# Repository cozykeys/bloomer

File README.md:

# CozyKeys Bloomer

This repository contains the design files for the CozyKeys Bloomer, an 87-key
ergonomic mechanical keyboard.

This keyboard has undergone several revisions and name changes. Previous names
were *Atreus87* and *Ergo87* and artifacts of these may still be present in the
repository.

## Firmware

- [Bloomer rev2](https://github.com/cozykeys/qmk_firmware/tree/bloomer_v2)
- [Bloomer rev3](https://github.com/cozykeys/qmk_firmware/tree/bloomer_v3)

## Project Status

### rev0

The first revision of the board was hand-wired and built as a proof of concept
to ensure that the layout is comfortable.

### rev1

The second revision added a PCB and a complete redesign of the case so that the
PCB would fit accurately.

This initial PCB was functional but lacked any RGB support. It also had a few
issues:
- When placing the ItsyBitsy upside down to reduce the height needed between
  the switch plate and bottom plate, there is no easy way to access RST
- Switch footprints were "flippable" which was misleading as the controller
  pinout only supported a single orientation

### rev2

The second revision added several features and fixes:
- Dedicated reset button with the case updated to make this accessible
- Single orientation switch footprints
- RGB underglow support

[Rev2 Build Guide](./revisions/rev2/README.md)

### rev3 (REDACTED)

See: [v3.0 README](./v3.0/README.md)

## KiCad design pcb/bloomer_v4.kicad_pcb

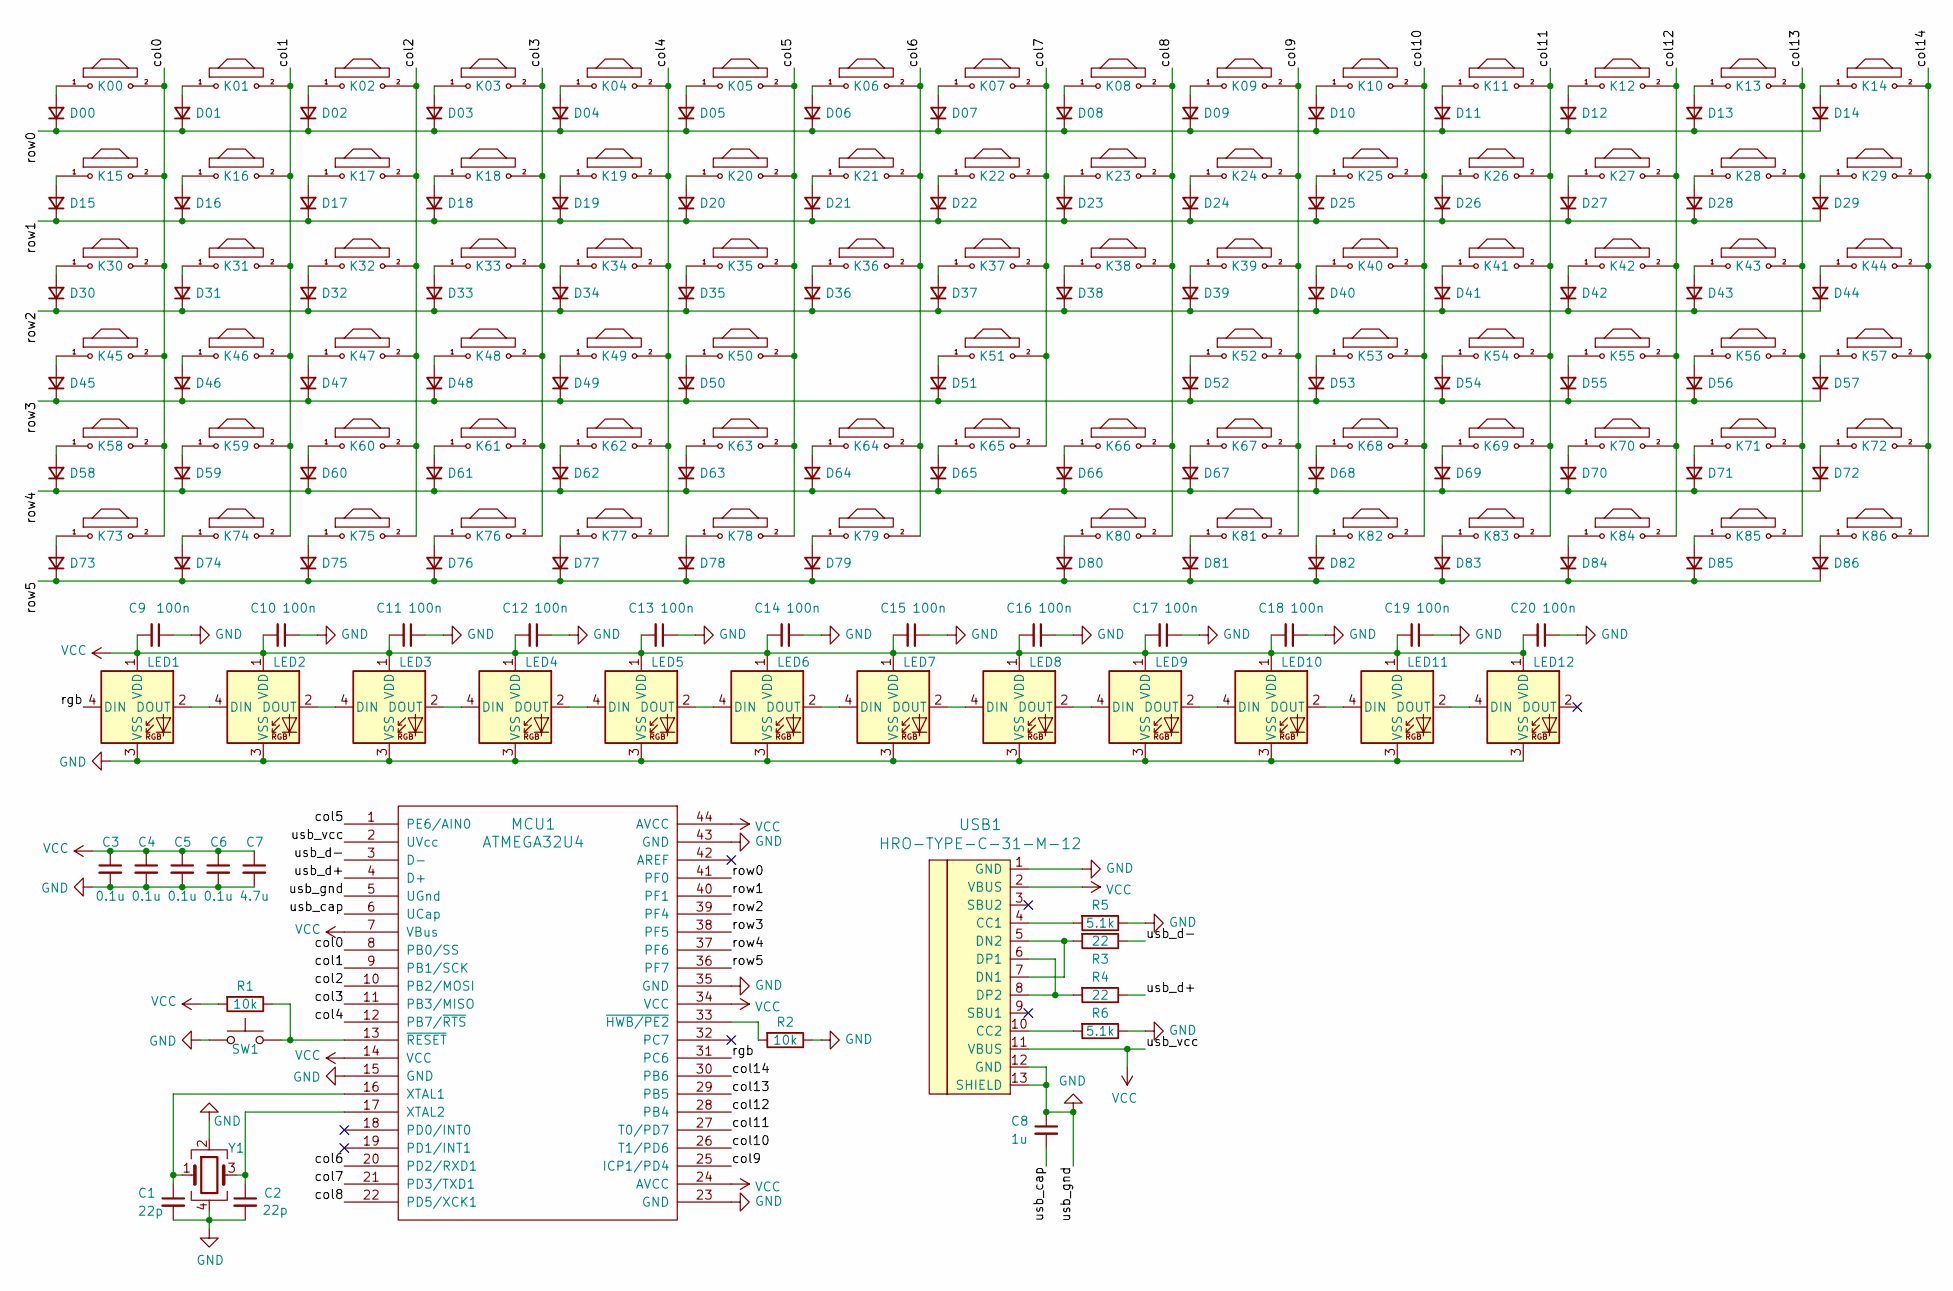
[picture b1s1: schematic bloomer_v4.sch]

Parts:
C1, C2: 22p; C_0805_2012Metric_Pad1.18x1.45mm_HandSolder
C3, C4, C5, C6: 0.1u; C_0805_2012Metric_Pad1.18x1.45mm_HandSolder
C7: 4.7u; C_0805_2012Metric_Pad1.18x1.45mm_HandSolder
C8: 1u; C_0805_2012Metric_Pad1.18x1.45mm_HandSolder
C9, C10, C11, C12, C13, C14, C15, C16, C17, C18, C19, C20: 100n; C_0805_2012Metric_Pad1.18x1.45mm_HandSolder
D00, D01, D02, D03, D04, D05, D06, D07, D08, D09, D10, D11, D12, D13, D14, D15, D16, D17, D18, D19, D20, D21, D22, D23, D24, D25, D26, D27, D28, D29, D30, D31, D32, D33, D34, D35, D36, D37, D38, D39, D40, D41, D42, D43, D44, D45, D46, D47, D48, D49, D50, D51, D52, D53, D54, D55, D56, D57, D58, D59, D60, D61, D62, D63, D64, D65, D66, D67, D68, D69, D70, D71, D72, D73, D74, D75, D76, D77, D78, D79, D80, D81, D82, D83, D84, D85, D86: D_Small; Diode-dual
K00, K01, K02, K03, K04, K05, K06, K07, K08, K09, K10, K11, K12, K13, K14, K15, K16, K17, K18, K19, K20, K21, K22, K23, K24, K25, K26, K27, K28, K29, K30, K31, K32, K33, K34, K35, K36, K37, K38, K39, K40, K41, K42, K43, K44, K45, K46, K47, K48, K49, K50, K51, K52, K53, K54, K55, K56, K57, K58, K59, K60, K61, K62, K63, K64, K65, K66, K67, K68, K69, K70, K71, K72, K73, K74, K75, K76, K77, K78, K79, K80, K81, K82, K83, K84, K85, K86: MX; MX_1.00u
LED1, LED2, LED3, LED4, LED5, LED6, LED7, LED8, LED9, LED10, LED11, LED12: WS2812B; LED_WS2812B_PLCC4_5.0x5.0mm_P3.2mm
MCU1: ATMEGA32U4; ATMEGA32U4-AU
R1, R2: 10k; R_0805_2012Metric_Pad1.20x1.40mm_HandSolder
R3, R4: 22; R_0805_2012Metric_Pad1.20x1.40mm_HandSolder
R5, R6: 5.1k; R_0805_2012Metric_Pad1.20x1.40mm_HandSolder
SW1: SW_Push; SW_TH_Tactile_Omron_B3F-10xx_Centered
USB1: HRO-TYPE-C-31-M-12; HRO-TYPE-C-31-M-12-Assembly
Y1: Crystal_GND24; Crystal_SMD_SeikoEpson_FA238-4Pin_3.2x2.5mm_HandSoldering

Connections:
/col0: K00.2, K15.2, K30.2, K45.2, K58.2, K73.2, MCU1.8 (PB0/SS)
/col1: K01.2, K16.2, K31.2, K46.2, K59.2, K74.2, MCU1.9 (PB1/SCK)
/col2: K02.2, K17.2, K32.2, K47.2, K60.2, K75.2, MCU1.10 (PB2/MOSI)
/col3: K03.2, K18.2, K33.2, K48.2, K61.2, K76.2, MCU1.11 (PB3/MISO)
/col4: K04.2, K19.2, K34.2, K49.2, K62.2, K77.2, MCU1.12 (PB7/~RTS)
/col5: K05.2, K20.2, K35.2, K50.2, K63.2, K78.2, MCU1.1 (PE6/AIN0)
/col6: K06.2, K21.2, K36.2, K64.2, K79.2, MCU1.20 (PD2/RXD1)
/col7: K07.2, K22.2, K37.2, K51.2, K65.2, MCU1.21 (PD3/TXD1)
/col8: K08.2, K23.2, K38.2, K66.2, K80.2, MCU1.22 (PD5/XCK1)
/col9: K09.2, K24.2, K39.2, K52.2, K67.2, K81.2, MCU1.25 (ICP1/PD4)
/col10: K10.2, K25.2, K40.2, K53.2, K68.2, K82.2, MCU1.26 (T1/PD6)
/col11: K11.2, K26.2, K41.2, K54.2, K69.2, K83.2, MCU1.27 (T0/PD7)
/col12: K12.2, K27.2, K42.2, K55.2, K70.2, K84.2, MCU1.28 (PB4)
/col13: K13.2, K28.2, K43.2, K56.2, K71.2, K85.2, MCU1.29 (PB5)
/col14: K14.2, K29.2, K44.2, K57.2, K72.2, K86.2, MCU1.30 (PB6)
/rgb: LED1.4 (DIN), MCU1.31 (PC6)
/row0: D00.1 (K), D01.1 (K), D02.1 (K), D03.1 (K), D04.1 (K), D05.1 (K), D06.1 (K), D07.1 (K), D08.1 (K), D09.1 (K), D10.1 (K), D11.1 (K), D12.1 (K), D13.1 (K), D14.1 (K), MCU1.41 (PF0)
/row1: D15.1 (K), D16.1 (K), D17.1 (K), D18.1 (K), D19.1 (K), D20.1 (K), D21.1 (K), D22.1 (K), D23.1 (K), D24.1 (K), D25.1 (K), D26.1 (K), D27.1 (K), D28.1 (K), D29.1 (K), MCU1.40 (PF1)
/row2: D30.1 (K), D31.1 (K), D32.1 (K), D33.1 (K), D34.1 (K), D35.1 (K), D36.1 (K), D37.1 (K), D38.1 (K), D39.1 (K), D40.1 (K), D41.1 (K), D42.1 (K), D43.1 (K), D44.1 (K), MCU1.39 (PF4)
/row3: D45.1 (K), D46.1 (K), D47.1 (K), D48.1 (K), D49.1 (K), D50.1 (K), D51.1 (K), D52.1 (K), D53.1 (K), D54.1 (K), D55.1 (K), D56.1 (K), D57.1 (K), MCU1.38 (PF5)
/row4: D58.1 (K), D59.1 (K), D60.1 (K), D61.1 (K), D62.1 (K), D63.1 (K), D64.1 (K), D65.1 (K), D66.1 (K), D67.1 (K), D68.1 (K), D69.1 (K), D70.1 (K), D71.1 (K), D72.1 (K), MCU1.37 (PF6)
/row5: D73.1 (K), D74.1 (K), D75.1 (K), D76.1 (K), D77.1 (K), D78.1 (K), D79.1 (K), D80.1 (K), D81.1 (K), D82.1 (K), D83.1 (K), D84.1 (K), D85.1 (K), D86.1 (K), MCU1.36 (PF7)
/usb_cap: C8.2, MCU1.6 (UCap)
/usb_d+: MCU1.4 (D+), R4.1
/usb_d-: MCU1.3 (D-), R3.1
GND: C1.2, C2.2, C3.2, C4.2, C5.2, C6.2, C7.2, C8.1, C9.1, C10.1, C11.1, C12.1, C13.1, C14.1, C15.1, C16.1, C17.1, C18.1, C19.1, C20.1, LED1.3 (VSS), LED2.3 (VSS), LED3.3 (VSS), LED4.3 (VSS), LED5.3 (VSS), LED6.3 (VSS), LED7.3 (VSS), LED8.3 (VSS), LED9.3 (VSS), LED10.3 (VSS), LED11.3 (VSS), LED12.3 (VSS), MCU1.5 (UGnd), MCU1.15 (GND), MCU1.23 (GND), MCU1.35 (GND), MCU1.43 (GND), R2.1, R5.1, R6.1, SW1.1, USB1.1 (GND), USB1.12 (GND), USB1.13 (SHIELD), Y1.2, Y1.4
unnamed: C1.1, MCU1.16 (XTAL1), Y1.1
unnamed: C2.1, MCU1.17 (XTAL2), Y1.3
unnamed: D00.2 (A), K00.1
unnamed: D01.2 (A), K01.1
unnamed: D02.2 (A), K02.1
unnamed: D03.2 (A), K03.1
unnamed: D04.2 (A), K04.1
unnamed: D05.2 (A), K05.1
unnamed: D06.2 (A), K06.1
unnamed: D07.2 (A), K07.1
unnamed: D08.2 (A), K08.1
unnamed: D09.2 (A), K09.1
unnamed: D10.2 (A), K10.1
unnamed: D11.2 (A), K11.1
unnamed: D12.2 (A), K12.1
unnamed: D13.2 (A), K13.1
unnamed: D14.2 (A), K14.1
unnamed: D15.2 (A), K15.1
unnamed: D16.2 (A), K16.1
unnamed: D17.2 (A), K17.1
unnamed: D18.2 (A), K18.1
unnamed: D19.2 (A), K19.1
unnamed: D20.2 (A), K20.1
unnamed: D21.2 (A), K21.1
unnamed: D22.2 (A), K22.1
unnamed: D23.2 (A), K23.1
unnamed: D24.2 (A), K24.1
unnamed: D25.2 (A), K25.1
unnamed: D26.2 (A), K26.1
unnamed: D27.2 (A), K27.1
unnamed: D28.2 (A), K28.1
unnamed: D29.2 (A), K29.1
unnamed: D30.2 (A), K30.1
unnamed: D31.2 (A), K31.1
unnamed: D32.2 (A), K32.1
unnamed: D33.2 (A), K33.1
unnamed: D34.2 (A), K34.1
unnamed: D35.2 (A), K35.1
unnamed: D36.2 (A), K36.1
unnamed: D37.2 (A), K37.1
unnamed: D38.2 (A), K38.1
unnamed: D39.2 (A), K39.1
unnamed: D40.2 (A), K40.1
unnamed: D41.2 (A), K41.1
unnamed: D42.2 (A), K42.1
unnamed: D43.2 (A), K43.1
unnamed: D44.2 (A), K44.1
unnamed: D45.2 (A), K45.1
unnamed: D46.2 (A), K46.1
unnamed: D47.2 (A), K47.1
unnamed: D48.2 (A), K48.1
unnamed: D49.2 (A), K49.1
unnamed: D50.2 (A), K50.1
unnamed: D51.2 (A), K51.1
unnamed: D52.2 (A), K52.1
unnamed: D53.2 (A), K53.1
unnamed: D54.2 (A), K54.1
unnamed: D55.2 (A), K55.1
unnamed: D56.2 (A), K56.1
unnamed: D57.2 (A), K57.1
unnamed: D58.2 (A), K58.1
unnamed: D59.2 (A), K59.1
unnamed: D60.2 (A), K60.1
unnamed: D61.2 (A), K61.1
unnamed: D62.2 (A), K62.1
unnamed: D63.2 (A), K63.1
unnamed: D64.2 (A), K64.1
unnamed: D65.2 (A), K65.1
unnamed: D66.2 (A), K66.1
unnamed: D67.2 (A), K67.1
unnamed: D68.2 (A), K68.1
unnamed: D69.2 (A), K69.1
unnamed: D70.2 (A), K70.1
unnamed: D71.2 (A), K71.1
unnamed: D72.2 (A), K72.1
unnamed: D73.2 (A), K73.1
unnamed: D74.2 (A), K74.1
unnamed: D75.2 (A), K75.1
unnamed: D76.2 (A), K76.1
unnamed: D77.2 (A), K77.1
unnamed: D78.2 (A), K78.1
unnamed: D79.2 (A), K79.1
unnamed: D80.2 (A), K80.1
unnamed: D81.2 (A), K81.1
unnamed: D82.2 (A), K82.1
unnamed: D83.2 (A), K83.1
unnamed: D84.2 (A), K84.1
unnamed: D85.2 (A), K85.1
unnamed: D86.2 (A), K86.1
unnamed: LED1.2 (DOUT), LED2.4 (DIN)
unnamed: LED2.2 (DOUT), LED3.4 (DIN)
unnamed: LED3.2 (DOUT), LED4.4 (DIN)
unnamed: LED4.2 (DOUT), LED5.4 (DIN)
unnamed: LED5.2 (DOUT), LED6.4 (DIN)
unnamed: LED6.2 (DOUT), LED7.4 (DIN)
unnamed: LED7.2 (DOUT), LED8.4 (DIN)
unnamed: LED8.2 (DOUT), LED9.4 (DIN)
unnamed: LED10.2 (DOUT), LED11.4 (DIN)
unnamed: LED9.2 (DOUT), LED10.4 (DIN)
unnamed: LED11.2 (DOUT), LED12.4 (DIN)
unnamed: MCU1.13 (~RESET), R1.1, SW1.2
unnamed: MCU1.33 (~HWB/PE2), R2.2
unnamed: R3.2, USB1.5 (DN2), USB1.7 (DN1)
unnamed: R4.2, USB1.6 (DP1), USB1.8 (DP2)
unnamed: R5.2, USB1.4 (CC1)
unnamed: R6.2, USB1.10 (CC2)
VCC: C3.1, C4.1, C5.1, C6.1, C7.1, C9.2, C10.2, C11.2, C12.2, C13.2, C14.2, C15.2, C16.2, C17.2, C18.2, C19.2, C20.2, LED1.1 (VDD), LED2.1 (VDD), LED3.1 (VDD), LED4.1 (VDD), LED5.1 (VDD), LED6.1 (VDD), LED7.1 (VDD), LED8.1 (VDD), LED9.1 (VDD), LED10.1 (VDD), LED11.1 (VDD), LED12.1 (VDD), MCU1.2 (UVcc), MCU1.7 (VBus), MCU1.14 (VCC), MCU1.24 (AVCC), MCU1.34 (VCC), MCU1.44 (AVCC), R1.2, USB1.2 (VBUS), USB1.11 (VBUS)

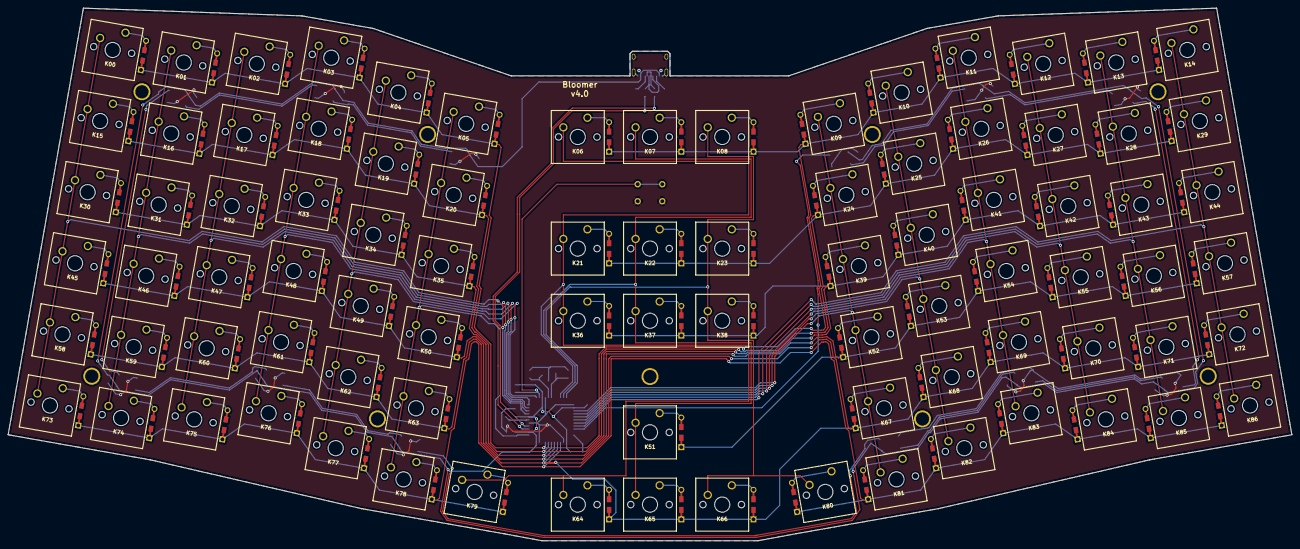
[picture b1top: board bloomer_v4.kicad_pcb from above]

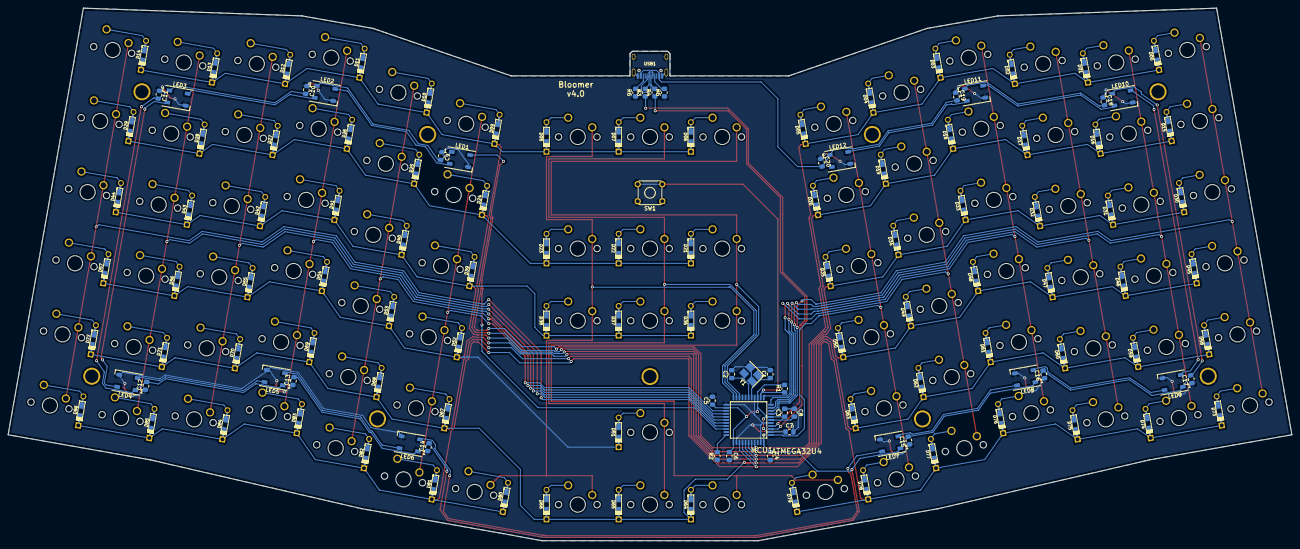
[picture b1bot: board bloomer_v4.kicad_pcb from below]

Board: 2 copper layers, 338.7 x 140.5 mm, 225 parts (138 on the bottom side), 133 nets.

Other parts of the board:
H1, H2, H3, H4, H5, H6, H7, H8, H9: VAL**; HOLE_M2_SPACER

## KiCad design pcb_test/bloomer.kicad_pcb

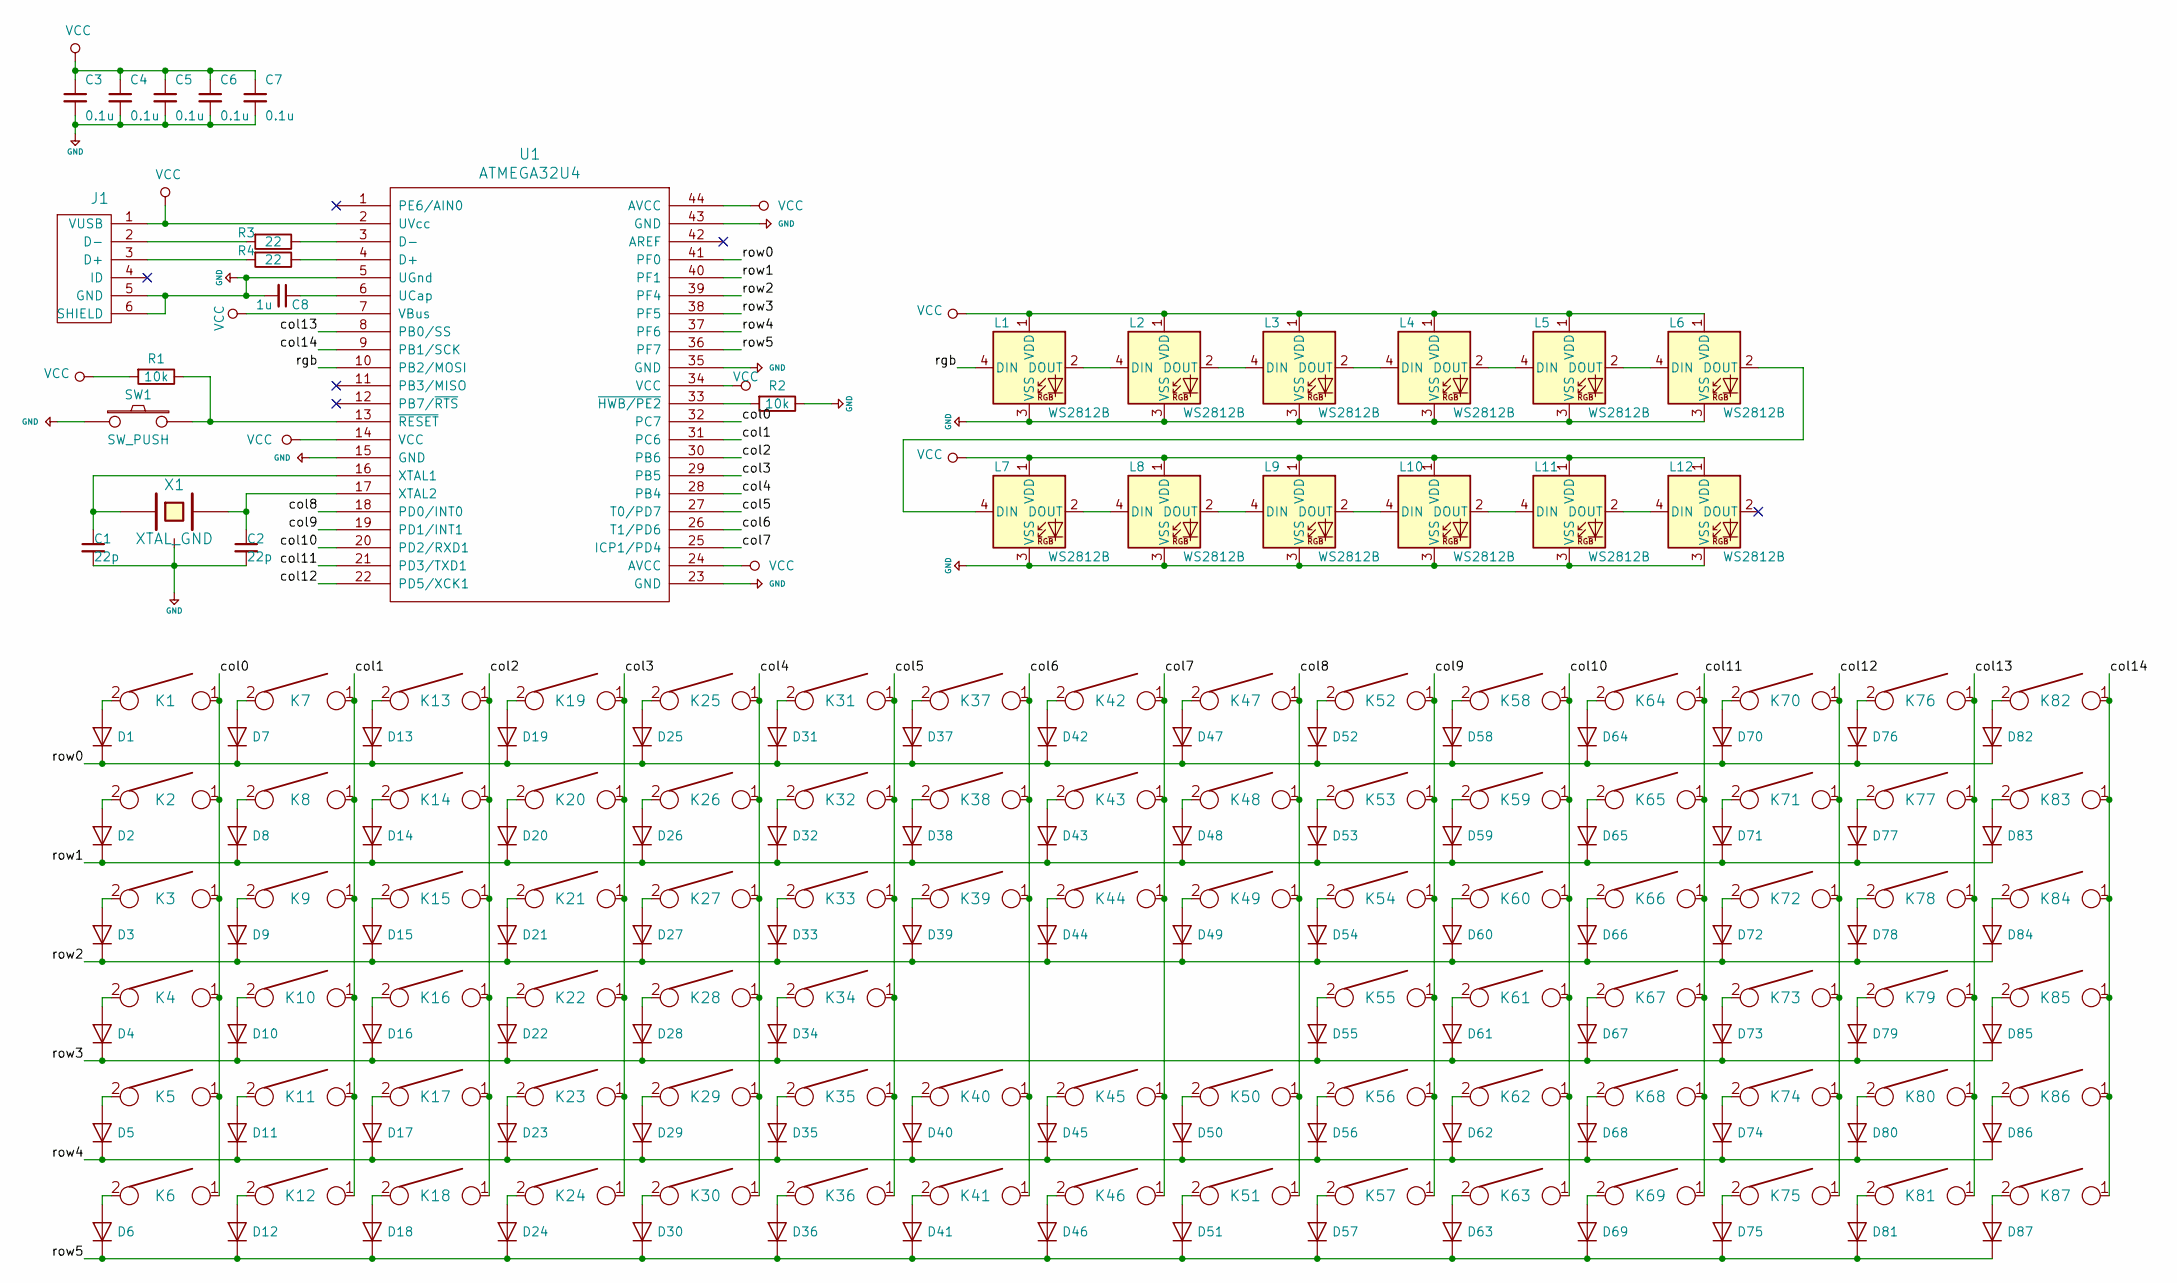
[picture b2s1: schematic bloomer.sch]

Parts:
C1, C2: 22p; C_0805_2012Metric_Pad1.15x1.40mm_HandSolder
C3, C4, C5, C6, C7: 0.1u; C_0805_2012Metric_Pad1.15x1.40mm_HandSolder
C8: 1u; C_0805_2012Metric_Pad1.15x1.40mm_HandSolder
D1, D2, D3, D4, D5, D6, D7, D8, D9, D10, D11, D12, D13, D14, D15, D16, D17, D18, D19, D20, D21, D22, D23, D24, D25, D26, D27, D28, D29, D30, D31, D32, D33, D34, D35, D36, D37, D38, D39, D40, D41, D42, D43, D44, D45, D46, D47, D48, D49, D50, D51, D52, D53, D54, D55, D56, D57, D58, D59, D60, D61, D62, D63, D64, D65, D66, D67, D68, D69, D70, D71, D72, D73, D74, D75, D76, D77, D78, D79, D80, D81, D82, D83, D84, D85, D86, D87: D; D_SOD123_axial
J1: USB_mini_micro_B; USB_miniB_hirose_5S8
K1, K2, K3, K4, K5, K6, K7, K8, K9, K10, K11, K12, K13, K14, K15, K16, K17, K18, K19, K20, K21, K22, K23, K24, K25, K26, K27, K28, K29, K30, K31, K32, K33, K34, K35, K36, K37, K38, K39, K40, K41, K42, K43, K44, K45, K46, K47, K48, K49, K50, K51, K52, K53, K54, K55, K56, K57, K58, K59, K60, K61, K62, K63, K64, K65, K66, K67, K68, K69, K70, K71, K72, K73, K74, K75, K76, K77, K78, K79, K80, K81, K82, K83, K84, K85, K86, K87: KEYSW; Mx_Alps_100
L1, L2, L3, L4, L5, L6, L7, L8, L9, L10, L11, L12: WS2812B; LED_WS2812B_PLCC4_5.0x5.0mm_P3.2mm
R1, R2: 10k; R_0805_2012Metric_Pad1.15x1.40mm_HandSolder
R3, R4: 22; R_0805_2012Metric_Pad1.15x1.40mm_HandSolder
SW1: SW_PUSH; SW_SPST_TL3342
U1: ATMEGA32U4; TQFP-44_10x10mm_P0.8mm
X1: XTAL_GND; Crystal_SMD_TXC_7M-4Pin_3.2x2.5mm_HandSoldering

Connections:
+5V: C1.2, C2.2, C3.2, C4.2, C5.2, C6.2, C7.2, C8.2, J1.5 (GND), J1.6 (SHIELD), L1.3 (VSS), L2.3 (VSS), L3.3 (VSS), L4.3 (VSS), L5.3 (VSS), L6.3 (VSS), L7.3 (VSS), L8.3 (VSS), L9.3 (VSS), L10.3 (VSS), L11.3 (VSS), L12.3 (VSS), R2.1, SW1.1, U1.5 (UGnd), U1.15 (GND), U1.23 (GND), U1.35 (GND), U1.43 (GND), X1.3
/col0: K1.1, K2.1, K3.1, K4.1, K5.1, K6.1, U1.32 (PC7)
/col1: K7.1, K8.1, K9.1, K10.1, K11.1, K12.1, U1.31 (PC6)
/col2: K13.1, K14.1, K15.1, K16.1, K17.1, K18.1, U1.30 (PB6)
/col3: K19.1, K20.1, K21.1, K22.1, K23.1, K24.1, U1.29 (PB5)
/col4: K25.1, K26.1, K27.1, K28.1, K29.1, K30.1, U1.28 (PB4)
/col5: K31.1, K32.1, K33.1, K34.1, K35.1, K36.1, U1.27 (T0/PD7)
/col6: K37.1, K38.1, K39.1, K40.1, K41.1, U1.26 (T1/PD6)
/col7: K42.1, K43.1, K44.1, K45.1, K46.1, U1.25 (ICP1/PD4)
/col8: K47.1, K48.1, K49.1, K50.1, K51.1, U1.18 (PD0/INT0)
/col9: K52.1, K53.1, K54.1, K55.1, K56.1, K57.1, U1.19 (PD1/INT1)
/col10: K58.1, K59.1, K60.1, K61.1, K62.1, K63.1, U1.20 (PD2/RXD1)
/col11: K64.1, K65.1, K66.1, K67.1, K68.1, K69.1, U1.21 (PD3/TXD1)
/col12: K70.1, K71.1, K72.1, K73.1, K74.1, K75.1, U1.22 (PD5/XCK1)
/col13: K76.1, K77.1, K78.1, K79.1, K80.1, K81.1, U1.8 (PB0/SS)
/rgb: L1.4 (DIN), U1.10 (PB2/MOSI)
/row0: D1.1 (K), D7.1 (K), D13.1 (K), D19.1 (K), D25.1 (K), D31.1 (K), D37.1 (K), D42.1 (K), D47.1 (K), D52.1 (K), D58.1 (K), D64.1 (K), D70.1 (K), D76.1 (K), D82.1 (K), U1.41 (PF0)
/row1: D2.1 (K), D8.1 (K), D14.1 (K), D20.1 (K), D26.1 (K), D32.1 (K), D38.1 (K), D43.1 (K), D48.1 (K), D53.1 (K), D59.1 (K), D65.1 (K), D71.1 (K), D77.1 (K), D83.1 (K), U1.40 (PF1)
/row2: D3.1 (K), D9.1 (K), D15.1 (K), D21.1 (K), D27.1 (K), D33.1 (K), D39.1 (K), D44.1 (K), D49.1 (K), D54.1 (K), D60.1 (K), D66.1 (K), D72.1 (K), D78.1 (K), D84.1 (K), U1.39 (PF4)
/row3: D4.1 (K), D10.1 (K), D16.1 (K), D22.1 (K), D28.1 (K), D34.1 (K), D55.1 (K), D61.1 (K), D67.1 (K), D73.1 (K), D79.1 (K), D85.1 (K), U1.38 (PF5)
/row4: D5.1 (K), D11.1 (K), D17.1 (K), D23.1 (K), D29.1 (K), D35.1 (K), D40.1 (K), D45.1 (K), D50.1 (K), D56.1 (K), D62.1 (K), D68.1 (K), D74.1 (K), D80.1 (K), D86.1 (K), U1.37 (PF6)
/row5: D6.1 (K), D12.1 (K), D18.1 (K), D24.1 (K), D30.1 (K), D36.1 (K), D41.1 (K), D46.1 (K), D51.1 (K), D57.1 (K), D63.1 (K), D69.1 (K), D75.1 (K), D81.1 (K), D87.1 (K), U1.36 (PF7)
unnamed: C1.1, U1.16 (XTAL1), X1.1
unnamed: C2.1, U1.17 (XTAL2), X1.2
unnamed: C8.1, U1.6 (UCap)
unnamed: D1.2 (A), K1.2
unnamed: D2.2 (A), K2.2
unnamed: D3.2 (A), K3.2
unnamed: D4.2 (A), K4.2
unnamed: D5.2 (A), K5.2
unnamed: D6.2 (A), K6.2
unnamed: D7.2 (A), K7.2
unnamed: D8.2 (A), K8.2
unnamed: D9.2 (A), K9.2
unnamed: D10.2 (A), K10.2
unnamed: D11.2 (A), K11.2
unnamed: D12.2 (A), K12.2
unnamed: D13.2 (A), K13.2
unnamed: D14.2 (A), K14.2
unnamed: D15.2 (A), K15.2
unnamed: D16.2 (A), K16.2
unnamed: D17.2 (A), K17.2
unnamed: D18.2 (A), K18.2
unnamed: D19.2 (A), K19.2
unnamed: D20.2 (A), K20.2
unnamed: D21.2 (A), K21.2
unnamed: D22.2 (A), K22.2
unnamed: D23.2 (A), K23.2
unnamed: D24.2 (A), K24.2
unnamed: D25.2 (A), K25.2
unnamed: D26.2 (A), K26.2
unnamed: D27.2 (A), K27.2
unnamed: D28.2 (A), K28.2
unnamed: D29.2 (A), K29.2
unnamed: D30.2 (A), K30.2
unnamed: D31.2 (A), K31.2
unnamed: D32.2 (A), K32.2
unnamed: D33.2 (A), K33.2
unnamed: D34.2 (A), K34.2
unnamed: D35.2 (A), K35.2
unnamed: D36.2 (A), K36.2
unnamed: D37.2 (A), K37.2
unnamed: D38.2 (A), K38.2
unnamed: D39.2 (A), K39.2
unnamed: D40.2 (A), K40.2
unnamed: D41.2 (A), K41.2
unnamed: D42.2 (A), K42.2
unnamed: D43.2 (A), K43.2
unnamed: D44.2 (A), K44.2
unnamed: D45.2 (A), K45.2
unnamed: D46.2 (A), K46.2
unnamed: D47.2 (A), K47.2
unnamed: D48.2 (A), K48.2
unnamed: D49.2 (A), K49.2
unnamed: D50.2 (A), K50.2
unnamed: D51.2 (A), K51.2
unnamed: D52.2 (A), K52.2
unnamed: D53.2 (A), K53.2
unnamed: D54.2 (A), K54.2
unnamed: D55.2 (A), K55.2
unnamed: D56.2 (A), K56.2
unnamed: D57.2 (A), K57.2
unnamed: D58.2 (A), K58.2
unnamed: D59.2 (A), K59.2
unnamed: D60.2 (A), K60.2
unnamed: D61.2 (A), K61.2
unnamed: D62.2 (A), K62.2
unnamed: D63.2 (A), K63.2
unnamed: D64.2 (A), K64.2
unnamed: D65.2 (A), K65.2
unnamed: D66.2 (A), K66.2
unnamed: D67.2 (A), K67.2
unnamed: D68.2 (A), K68.2
unnamed: D69.2 (A), K69.2
unnamed: D70.2 (A), K70.2
unnamed: D71.2 (A), K71.2
unnamed: D72.2 (A), K72.2
unnamed: D73.2 (A), K73.2
unnamed: D74.2 (A), K74.2
unnamed: D75.2 (A), K75.2
unnamed: D76.2 (A), K76.2
unnamed: D77.2 (A), K77.2
unnamed: D78.2 (A), K78.2
unnamed: D79.2 (A), K79.2
unnamed: D80.2 (A), K80.2
unnamed: D81.2 (A), K81.2
unnamed: D82.2 (A), K82.2
unnamed: D83.2 (A), K83.2
unnamed: D84.2 (A), K84.2
unnamed: D85.2 (A), K85.2
unnamed: D86.2 (A), K86.2
unnamed: D87.2 (A), K87.2
unnamed: J1.2 (D-), R3.2
unnamed: J1.3 (D+), R4.2
unnamed: L1.2 (DOUT), L2.4 (DIN)
unnamed: L2.2 (DOUT), L3.4 (DIN)
unnamed: L3.2 (DOUT), L4.4 (DIN)
unnamed: L4.2 (DOUT), L5.4 (DIN)
unnamed: L5.2 (DOUT), L6.4 (DIN)
unnamed: L6.2 (DOUT), L7.4 (DIN)
unnamed: L7.2 (DOUT), L8.4 (DIN)
unnamed: L8.2 (DOUT), L9.4 (DIN)
unnamed: L10.2 (DOUT), L11.4 (DIN)
unnamed: L9.2 (DOUT), L10.4 (DIN)
unnamed: L11.2 (DOUT), L12.4 (DIN)
unnamed: R1.1, SW1.2, U1.13 (~RESET)
unnamed: R2.2, U1.33 (~HWB/PE2)
unnamed: R3.1, U1.3 (D-)
unnamed: R4.1, U1.4 (D+)
VCC: C3.1, C4.1, C5.1, C6.1, C7.1, J1.1 (VUSB), L1.1 (VDD), L2.1 (VDD), L3.1 (VDD), L4.1 (VDD), L5.1 (VDD), L6.1 (VDD), L7.1 (VDD), L8.1 (VDD), L9.1 (VDD), L10.1 (VDD), L11.1 (VDD), L12.1 (VDD), R1.2, U1.2 (UVcc), U1.7 (VBus), U1.14 (VCC), U1.24 (AVCC), U1.34 (VCC), U1.44 (AVCC)

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
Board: 2 copper layers, 202 parts (115 on the bottom side), 131 nets, no tracks yet.

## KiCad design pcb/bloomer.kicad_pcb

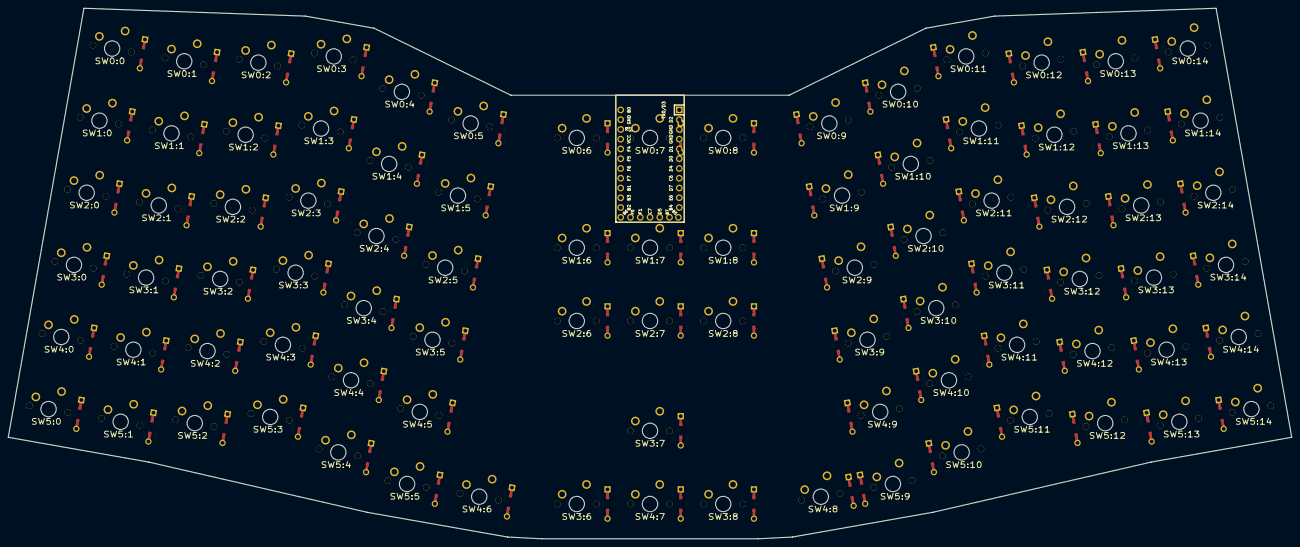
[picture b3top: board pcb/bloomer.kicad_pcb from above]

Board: 2 copper layers, 333.9 x 138.0 mm, 175 parts (1 on the bottom side), 108 nets, no tracks yet.

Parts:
D0:0, D0:1, D0:2, D0:3, D0:4, D0:5, D0:6, D0:7, D0:8, D0:9, D0:10, D0:11, D0:12, D0:13, D0:14, D1:0, D1:1, D1:2, D1:3, D1:4, D1:5, D1:6, D1:7, D1:8, D1:9, D1:10, D1:11, D1:12, D1:13, D1:14, D2:0, D2:1, D2:2, D2:3, D2:4, D2:5, D2:6, D2:7, D2:8, D2:9, D2:10, D2:11, D2:12, D2:13, D2:14, D3:0, D3:1, D3:2, D3:3, D3:4, D3:5, D3:6, D3:7, D3:8, D3:9, D3:10, D3:11, D3:12, D3:13, D3:14, D4:0, D4:1, D4:2, D4:3, D4:4, D4:5, D4:6, D4:7, D4:8, D4:9, D4:10, D4:11, D4:12, D4:13, D4:14, D5:0, D5:1, D5:2, D5:3, D5:4, D5:5, D5:9, D5:10, D5:11, D5:12, D5:13, D5:14: DIODE
SW0:0, SW0:1, SW0:2, SW0:3, SW0:4, SW0:5, SW0:6, SW0:7, SW0:8, SW0:9, SW0:10, SW0:11, SW0:12, SW0:13, SW0:14, SW1:0, SW1:1, SW1:2, SW1:3, SW1:4, SW1:5, SW1:6, SW1:7, SW1:8, SW1:9, SW1:10, SW1:11, SW1:12, SW1:13, SW1:14, SW2:0, SW2:1, SW2:2, SW2:3, SW2:4, SW2:5, SW2:6, SW2:7, SW2:8, SW2:9, SW2:10, SW2:11, SW2:12, SW2:13, SW2:14, SW3:0, SW3:1, SW3:2, SW3:3, SW3:4, SW3:5, SW3:6, SW3:7, SW3:8, SW3:9, SW3:10, SW3:11, SW3:12, SW3:13, SW3:14, SW4:0, SW4:1, SW4:2, SW4:3, SW4:4, SW4:5, SW4:6, SW4:7, SW4:8, SW4:9, SW4:10, SW4:11, SW4:12, SW4:13, SW4:14, SW5:0, SW5:1, SW5:2, SW5:3, SW5:4, SW5:5, SW5:9, SW5:10, SW5:11, SW5:12, SW5:13, SW5:14: MX
U1: Elite-C

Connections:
N-col-0: SW0:0.2, SW1:0.2, SW2:0.2, SW3:0.2, SW4:0.2, SW5:0.2
N-col-1: SW0:1.2, SW1:1.2, SW2:1.2, SW3:1.2, SW4:1.2, SW5:1.2
N-col-2: SW0:2.2, SW1:2.2, SW2:2.2, SW3:2.2, SW4:2.2, SW5:2.2
N-col-3: SW0:3.2, SW1:3.2, SW2:3.2, SW3:3.2, SW4:3.2, SW5:3.2
N-col-4: SW0:4.2, SW1:4.2, SW2:4.2, SW3:4.2, SW4:4.2, SW5:4.2
N-col-5: SW0:5.2, SW1:5.2, SW2:5.2, SW3:5.2, SW4:5.2, SW5:5.2
N-col-6: SW0:6.2, SW1:6.2, SW2:6.2, SW3:6.2, SW4:6.2
N-col-7: SW0:7.2, SW1:7.2, SW2:7.2, SW3:7.2, SW4:7.2
N-col-8: SW0:8.2, SW1:8.2, SW2:8.2, SW3:8.2, SW4:8.2
N-col-9: SW0:9.2, SW1:9.2, SW2:9.2, SW3:9.2, SW4:9.2, SW5:9.2
N-col-10: SW0:10.2, SW1:10.2, SW2:10.2, SW3:10.2, SW4:10.2, SW5:10.2
N-col-11: SW0:11.2, SW1:11.2, SW2:11.2, SW3:11.2, SW4:11.2, SW5:11.2
N-col-12: SW0:12.2, SW1:12.2, SW2:12.2, SW3:12.2, SW4:12.2, SW5:12.2
N-col-13: SW0:13.2, SW1:13.2, SW2:13.2, SW3:13.2, SW4:13.2, SW5:13.2
N-col-14: SW0:14.2, SW1:14.2, SW2:14.2, SW3:14.2, SW4:14.2, SW5:14.2
N-diode-0-0: D0:0.2, SW0:0.1
N-diode-0-1: D0:1.2, SW0:1.1
N-diode-0-2: D0:2.2, SW0:2.1
N-diode-0-3: D0:3.2, SW0:3.1
N-diode-0-4: D0:4.2, SW0:4.1
N-diode-0-5: D0:5.2, SW0:5.1
N-diode-0-6: D0:6.2, SW0:6.1
N-diode-0-7: D0:7.2, SW0:7.1
N-diode-0-8: D0:8.2, SW0:8.1
N-diode-0-9: D0:9.2, SW0:9.1
N-diode-0-10: D0:10.2, SW0:10.1
N-diode-0-11: D0:11.2, SW0:11.1
N-diode-0-12: D0:12.2, SW0:12.1
N-diode-0-13: D0:13.2, SW0:13.1
N-diode-0-14: D0:14.2, SW0:14.1
N-diode-1-0: D1:0.2, SW1:0.1
N-diode-1-1: D1:1.2, SW1:1.1
N-diode-1-2: D1:2.2, SW1:2.1
N-diode-1-3: D1:3.2, SW1:3.1
N-diode-1-4: D1:4.2, SW1:4.1
N-diode-1-5: D1:5.2, SW1:5.1
N-diode-1-6: D1:6.2, SW1:6.1
N-diode-1-7: D1:7.2, SW1:7.1
N-diode-1-8: D1:8.2, SW1:8.1
N-diode-1-9: D1:9.2, SW1:9.1
N-diode-1-10: D1:10.2, SW1:10.1
N-diode-1-11: D1:11.2, SW1:11.1
N-diode-1-12: D1:12.2, SW1:12.1
N-diode-1-13: D1:13.2, SW1:13.1
N-diode-1-14: D1:14.2, SW1:14.1
N-diode-2-0: D2:0.2, SW2:0.1
N-diode-2-1: D2:1.2, SW2:1.1
N-diode-2-2: D2:2.2, SW2:2.1
N-diode-2-3: D2:3.2, SW2:3.1
N-diode-2-4: D2:4.2, SW2:4.1
N-diode-2-5: D2:5.2, SW2:5.1
N-diode-2-6: D2:6.2, SW2:6.1
N-diode-2-7: D2:7.2, SW2:7.1
N-diode-2-8: D2:8.2, SW2:8.1
N-diode-2-9: D2:9.2, SW2:9.1
N-diode-2-10: D2:10.2, SW2:10.1
N-diode-2-11: D2:11.2, SW2:11.1
N-diode-2-12: D2:12.2, SW2:12.1
N-diode-2-13: D2:13.2, SW2:13.1
N-diode-2-14: D2:14.2, SW2:14.1
N-diode-3-0: D3:0.2, SW3:0.1
N-diode-3-1: D3:1.2, SW3:1.1
N-diode-3-2: D3:2.2, SW3:2.1
N-diode-3-3: D3:3.2, SW3:3.1
N-diode-3-4: D3:4.2, SW3:4.1
N-diode-3-5: D3:5.2, SW3:5.1
N-diode-3-6: D3:6.2, SW3:6.1
N-diode-3-7: D3:7.2, SW3:7.1
N-diode-3-8: D3:8.2, SW3:8.1
N-diode-3-9: D3:9.2, SW3:9.1
N-diode-3-10: D3:10.2, SW3:10.1
N-diode-3-11: D3:11.2, SW3:11.1
N-diode-3-12: D3:12.2, SW3:12.1
N-diode-3-13: D3:13.2, SW3:13.1
N-diode-3-14: D3:14.2, SW3:14.1
N-diode-4-0: D4:0.2, SW4:0.1
N-diode-4-1: D4:1.2, SW4:1.1
N-diode-4-2: D4:2.2, SW4:2.1
N-diode-4-3: D4:3.2, SW4:3.1
N-diode-4-4: D4:4.2, SW4:4.1
N-diode-4-5: D4:5.2, SW4:5.1
N-diode-4-6: D4:6.2, SW4:6.1
N-diode-4-7: D4:7.2, SW4:7.1
N-diode-4-8: D4:8.2, SW4:8.1
N-diode-4-9: D4:9.2, SW4:9.1
N-diode-4-10: D4:10.2, SW4:10.1
N-diode-4-11: D4:11.2, SW4:11.1
N-diode-4-12: D4:12.2, SW4:12.1
N-diode-4-13: D4:13.2, SW4:13.1
N-diode-4-14: D4:14.2, SW4:14.1
N-diode-5-0: D5:0.2, SW5:0.1
N-diode-5-1: D5:1.2, SW5:1.1
N-diode-5-2: D5:2.2, SW5:2.1
N-diode-5-3: D5:3.2, SW5:3.1
N-diode-5-4: D5:4.2, SW5:4.1
N-diode-5-5: D5:5.2, SW5:5.1
N-diode-5-9: D5:9.2, SW5:9.1
N-diode-5-10: D5:10.2, SW5:10.1
N-diode-5-11: D5:11.2, SW5:11.1
N-diode-5-12: D5:12.2, SW5:12.1
N-diode-5-13: D5:13.2, SW5:13.1
N-diode-5-14: D5:14.2, SW5:14.1
N-row-0: D0:0.1, D0:1.1, D0:2.1, D0:3.1, D0:4.1, D0:5.1, D0:6.1, D0:7.1, D0:8.1, D0:9.1, D0:10.1, D0:11.1, D0:12.1, D0:13.1, D0:14.1
N-row-1: D1:0.1, D1:1.1, D1:2.1, D1:3.1, D1:4.1, D1:5.1, D1:6.1, D1:7.1, D1:8.1, D1:9.1, D1:10.1, D1:11.1, D1:12.1, D1:13.1, D1:14.1
N-row-2: D2:0.1, D2:1.1, D2:2.1, D2:3.1, D2:4.1, D2:5.1, D2:6.1, D2:7.1, D2:8.1, D2:9.1, D2:10.1, D2:11.1, D2:12.1, D2:13.1, D2:14.1
N-row-3: D3:0.1, D3:1.1, D3:2.1, D3:3.1, D3:4.1, D3:5.1, D3:6.1, D3:7.1, D3:8.1, D3:9.1, D3:10.1, D3:11.1, D3:12.1, D3:13.1, D3:14.1
N-row-4: D4:0.1, D4:1.1, D4:2.1, D4:3.1, D4:4.1, D4:5.1, D4:6.1, D4:7.1, D4:8.1, D4:9.1, D4:10.1, D4:11.1, D4:12.1, D4:13.1, D4:14.1
N-row-5: D5:0.1, D5:1.1, D5:2.1, D5:3.1, D5:4.1, D5:5.1, D5:9.1, D5:10.1, D5:11.1, D5:12.1, D5:13.1, D5:14.1

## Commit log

2018-06-06 Add dimensions images
2018-06-10 Remove old source files
2018-06-15 Update readme to include new preview image
2018-06-15 Clean up the repository
2018-06-16 Update the published v1 files
2018-06-26 Make some major updates
    * Refactored some of the models
    * Refactored Deserialization
    * Added support for constants in the data file
    * Added support for layers in the data file
2018-06-26 Start implementing the path refactor
    * Add path and path component models
    * Start adding deserialization support
    * Add a script for finding quadratic control points
2018-06-27 Finish implementing path refactor
2018-07-04 Update keyboard layers
    Now that the format supports multiple layers, add the middle and bottom
    layers to the data file and update the paths to use the refactored path
    mechanisms.
2018-07-18 Rename instances in files
2018-07-18 Rename files
2018-07-18 Move kbutil to its own repository
2018-08-05 First revision of a PCB
    Also redesigned the case to better fit the PCB.
2018-08-07 Create LICENSE
2018-08-17 Add reset button footprint
2018-08-18 Start working on RGB underglow support
2018-08-18 Finish the rev2 features
2018-08-18 Add DXF files
2018-09-12 Rename Ergo87 to Bloomer and update readme
2019-03-19 Fix colors
2019-03-19 Updates for rev4
2019-03-19 Condense middle cluster
2019-03-19 Add preview
2019-03-23 Fix Z ordering
2019-03-25 Progress towards rev4
2019-03-25 Add kicad files for rev4
2019-04-15 Finish up rev3
2019-04-15 Remove ItsyBitsy footprint from case files
2019-04-26 Update legends for default layout
2019-04-26 Add a keycap kit recommendation
2019-05-11 Update plate
    - Resize screw holes around controller
    - Remove cutout around controller
    - Square off the corners
2019-05-11 Add reset switch to PCB
2019-05-11 Add rounding back to the plate corners
2019-05-11 Add layouts directory
2019-05-11 Ignore FCStd1 backup files
2019-05-11 Add FreeCAD case file
2019-05-11 Add screw inlays to case
2019-05-12 Add rev3.1 plate dxf
2019-08-06 Add generate script
2019-10-11 Reorganize files pre-merge
2019-10-11 Start working on v4.0
2019-10-12 Add firmware link to readme
2019-10-13 Finalize switch layout
2019-10-14 Progress
2019-10-14 Add v3 firmware link
2020-02-09 Add PCB overlay
2020-02-09 Progress!
2020-02-10 Update shell script usage
2020-02-14 Use new Visibility attribute instead of block comments
2020-02-14 Add notes
2020-03-08 Updaes
2020-07-05 Finalize switch data
2020-07-05 Fix row/column on thumb keys
2020-07-05 Add initial scripts directory
2020-07-05 Add build log
2020-07-05 Set SVG size in SvgWriter class
2020-07-05 Fix SVG so it displays on GitHub
2021-04-13 Add v2 build guide
2021-04-17 Add column offsets to markup diagram
2021-04-18 Finalize key layout
2021-04-21 Add default keymap SVGs
2021-04-21 Add default keymap SVGs (#14)
2022-08-07 add a basic build guide for rev2
2022-08-07 specify in title that it is the v2 build guide
2022-08-07 specify diode type
2022-08-07 provide example of reset button
2022-08-07 update grammar
2022-08-07 fix typo
2022-08-08 add note anout restting twice before flashing firmware
2022-08-08 add microsontroller to materials
2022-08-08 Add a basic build guide for rev2 (#16)
2024-12-21 Saving local changes
    I don't remember when I worked on this or what I was doing. These
    changes may even be bad or WIP but I'm committing them to avoid any
    unsaved local changes that could get lost.
